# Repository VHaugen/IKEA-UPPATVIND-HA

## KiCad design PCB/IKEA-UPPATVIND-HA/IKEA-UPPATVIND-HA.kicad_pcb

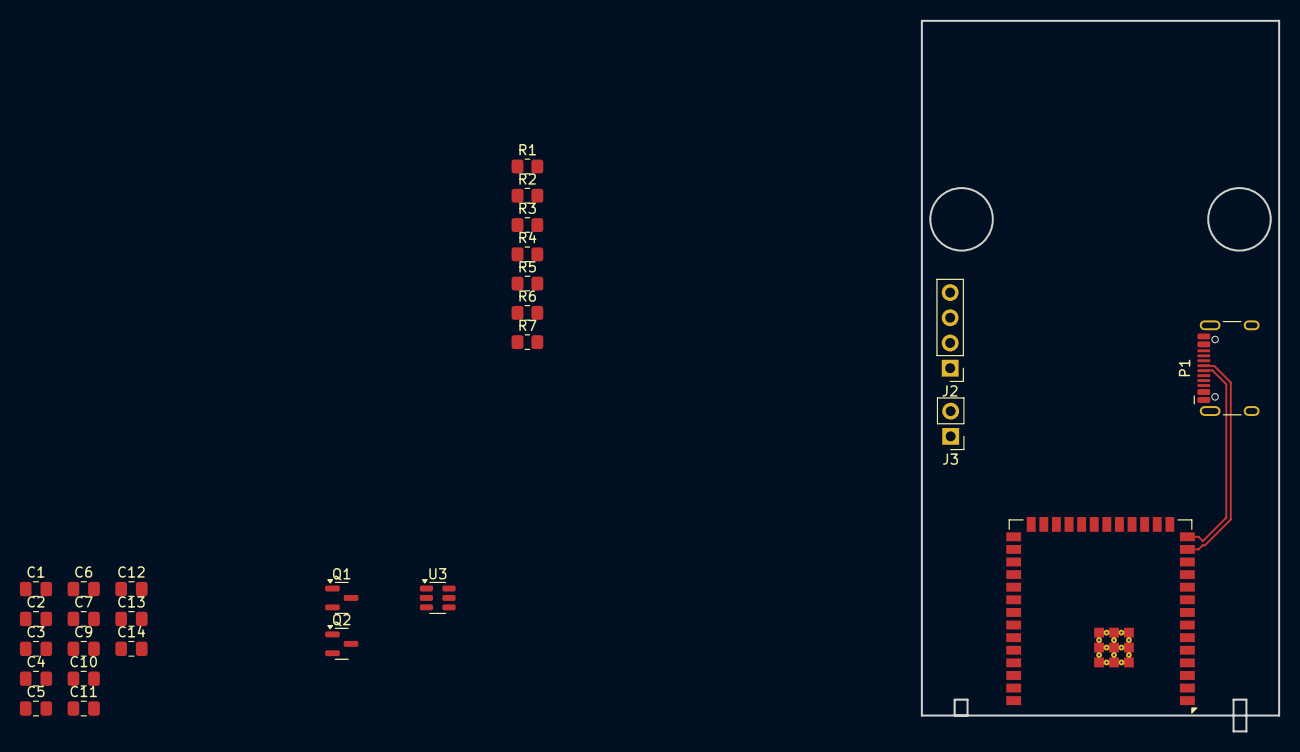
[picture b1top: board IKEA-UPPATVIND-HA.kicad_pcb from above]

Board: 2 copper layers, 36.0 x 71.6 mm, 27 parts (0 on the bottom side), 15 nets.

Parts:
C1, C3, C7, C10, C11, C14: 22uF; C_0805_2012Metric_Pad1.18x1.45mm_HandSolder
C2, C12: 100nF; C_0805_2012Metric_Pad1.18x1.45mm_HandSolder
C4, C5: 47pF; C_0805_2012Metric_Pad1.18x1.45mm_HandSolder
C6, C9, C13: 470uF; C_0805_2012Metric_Pad1.18x1.45mm_HandSolder
J2: Conn_01x04; PinHeader_1x04_P2.54mm_Vertical
J3: Conn_01x02; PinHeader_1x02_P2.54mm_Vertical
P1: USB_C_Plug_USB2.0; USB_C_Receptacle_HCTL_HC-TYPE-C-16P-01A
Q1, Q2: BSS138; SOT-23
R1, R2, R3, R4, R5: 10K; R_0805_2012Metric_Pad1.20x1.40mm_HandSolder
R6: 100K; R_0805_2012Metric_Pad1.20x1.40mm_HandSolder
R7: 13,7K; R_0805_2012Metric_Pad1.20x1.40mm_HandSolder
U1: ESP32-S3-WROOM-2
U3: TPS54202DDC; SOT-23-6

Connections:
+3.3V: C1.2, C2.2, C9.2, C10.2, Q1.1 (G), Q2.1 (G), R1.1, R2.2, R4.2, U1.2 (3V3)
+5V: C13.2, C14.2, R3.2, R5.2, R6.2
+24V: C6.2, C7.2, C11.2, J2.1, J3.1, U3.3 (VIN)
/FG: J2.4, Q2.3 (D), R5.1
/FG33: Q2.2 (S), R4.1, U1.6 (IO6)
/PWM: J2.3, Q1.3 (D), R3.1
/PWM33: Q1.2 (S), R2.1, U1.5 (IO5)
GND: C1.1, C2.1, C3.1, C4.1, C5.1, C6.1, C7.1, C9.1, C10.1, C11.1, C14.1, J2.2, J3.2, P1.A1 (GND), P1.A12 (GND), P1.B1 (GND), P1.B12 (GND), P1.S1 (SHIELD), R7.1, U1.1 (GND), U1.40 (GND), U1.41 (GND), U3.1 (GND)
unnamed: C3.2, R1.2, U1.3 (EN)
unnamed: C12.1, U3.6 (BOOT)
unnamed: C13.1, R6.1, R7.2, U3.4 (FB)
unnamed: C12.2, U3.2 (SW)
USBD+: C5.2, P1.A6 (D+), U1.14 (USB_D+/IO20)
USBD-: C4.2, P1.A7 (D-), U1.13 (USB_D-/IO19)
VBUS: P1.A4 (VBUS), P1.A9 (VBUS), P1.B4 (VBUS), P1.B9 (VBUS)

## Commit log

2024-09-09 INIT
    INIT
